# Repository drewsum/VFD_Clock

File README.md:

A VFD clock centered around a PIC32MZ EF microcontroller

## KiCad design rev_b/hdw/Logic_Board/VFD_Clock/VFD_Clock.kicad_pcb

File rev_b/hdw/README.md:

rev B control boards use rev A display boards

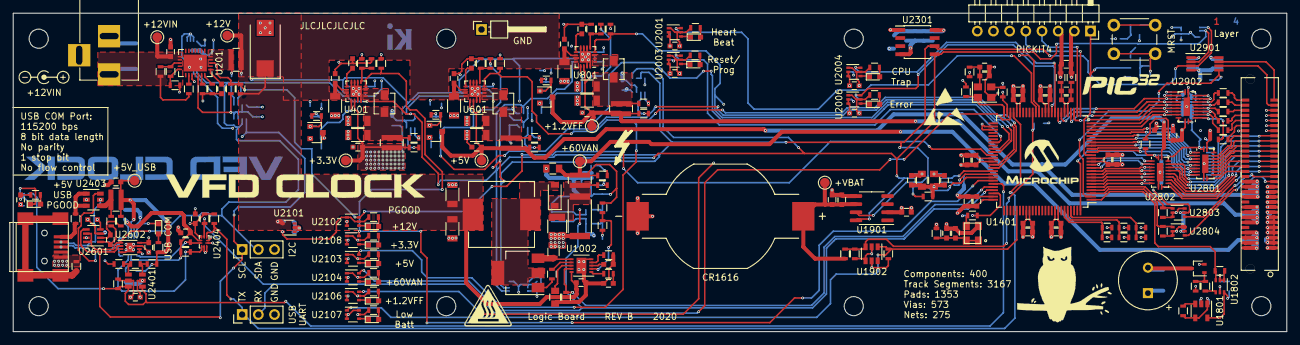
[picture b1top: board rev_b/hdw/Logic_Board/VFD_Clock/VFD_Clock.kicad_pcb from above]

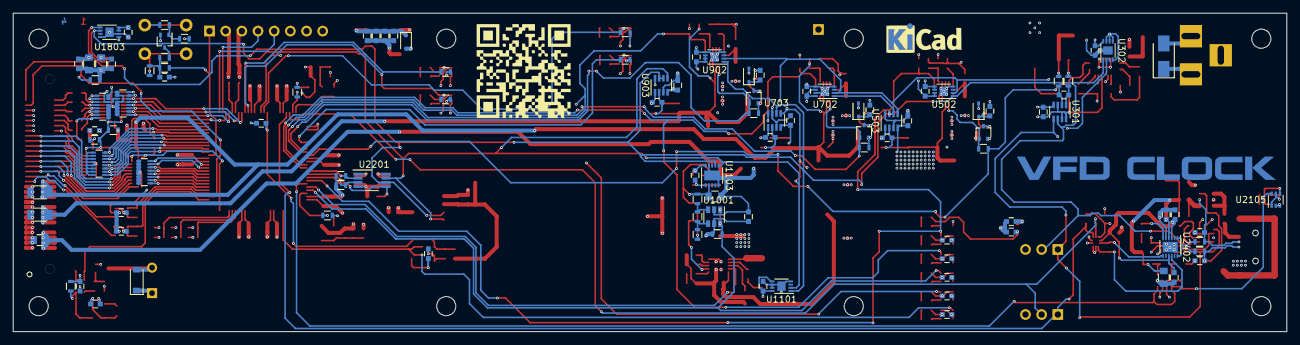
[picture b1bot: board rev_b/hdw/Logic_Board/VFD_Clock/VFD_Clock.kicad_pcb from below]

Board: 4 copper layers, 200.0 x 50.0 mm, 359 parts (109 on the bottom side), 209 nets.

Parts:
BT1902: CR1616_Holder; BAT_BU1632SM-JJ-GTR
BZ1801: CST-931RP-A; MagneticBuzzer_CUI_CST-931RP-A
C201, C402, C602, C802: 10nF; C_0603
C202, C301, C302, C303, C403, C406, C503, C504, C505, C603, C606, C703, C704, C705, C803, C806, C903, C904, C905, C1003, C1004, C1005, C1102, C1104, C1501, C1502, C1601, C1602, C1608, C1609, C1615, C1616, C1622, C1623, C1701, C1702, C1801, C1803, C1804, C1901, C1903, C1904, C1905, C2001, C2003, C2004, C2006, C2101, C2103, C2104, C2105, C2106, C2107, C2108, C2201, C2203, C2304, C2401, C2402, C2403, C2404, C2406, C2407, C2410, C2601, C2602, C2603, C2801, C2802, C2807, C2808, C2901, C2904, C2906: 0.1uF; C_0603
C205: 100uF; CP_Tantalum_Case-X_EIA-7343-43_Reflow
C401, C601, C801, C1001, C1002: 10uF; C_1206
C404, C405, C604, C605, C804, C805, C3002, C3003: 22uF; C_1206
C1007: 6.8nF; C_0603
C1009, C2202, C2204, C2405, C2905, C2907: 4.7uF; C_0805
C1010: 1uF; C_1210
C1011, C1105, C3001: 0.1uF; C_0805
C1301, C1302, C1303, C1603, C1604, C1605, C1606, C1607, C1610, C1617, C1624, C1703, C1704, C1902, C2102, C2301, C2302, C2303: 10uF; C_0603
C2408, C2409: 47pF; C_0603
D201: 24V; D_SMA
D1001, D1801: MBR0580; D_SOD-123
D1301, D1302, D1303, D2301: BAT48JFILM; D_SOD-323
D2001, D2101, D2102, D2103, D2104, D2105, D2107: Green; LED_0603
D2003, D2004, D2006, D2106: Red; LED_0603
D2401: Yellow; LED_0603
H3101, H3102, H3103, H3104, H3105, H3106, H3107, H3108: MountingHole; MountingHole_3mm
J201: +12V IN; BARREL_JACK
J1501: PICKIT4; PICKIT4_Header
J1801: I2C; Pin_Header_Straight_1x03_Pitch2.54mm
J1802: USB UART; Pin_Header_Straight_1x03_Pitch2.54mm
J2401: USB_B_Mini; USB_Mini-B
J3001: DSP_IO_Connector; ERF8-030-07.0-S-DV-K-TR
L401, L601, L801: 2.2uH; L_Vishay_IHLP-1212
L1001: 100uH; L_Vishay_IHLP-4040
L1601, L1602, L1701, L1702, L2401, L2402: 600R 0.5A; L_0603
Q1001: IRFL214TRPBF; SOT-223-3_TabPin2
Q1301, Q1304, Q1307, Q1501, Q1801: BSS214NW; SOT-323_SC-70
Q1302, Q1306, Q1308: ZXMS6004FFTA; SOT-23
R201: 51.1k; R_0603
R202: 1.15k; R_0603
R203, R209: 5.11k; R_0603
R204, R207, R211, R404, R604, R605, R804, R805, R1008, R1009, R1302, R1306, R1310, R1502, R1504, R1701, R1704, R1705, R1802, R1804, R1805, R1807, R1808, R1810, R1903, R2001, R2005, R2006, R2010, R2201, R2202, R2203, R2405, R2903: 10k; R_0603
R205, R210, R405, R407, R606, R608, R806, R808, R1014, R1016, R1501, R1803, R1806, R1809, R1811, R2406, R2410: 10; R_0603
R206, R406, R607, R807, R2407: 0.02; R_0612
R208: 13k; R_0603
R408: 562k; R_0603
R409: 180k; R_0603
R609: 10.5k; R_0603
R610: 2k; R_0603
R809: 75k; R_0603
R810: 150k; R_0603
R1003: 196k; R_0603
R1004: 237; R_0603
R1005: 1.2k; R_0603
R1007: 17.4k; R_0603
R1010: 22k; R_0603
R1011: 2; R_0603
R1012: 0.16; R_0805
R1013: 10k; R_2512
R1015: 1; R_0612
R1017: 36.5k; R_0603
R1018, R1505, R2003, R2007, R2008, R2012, R2101, R2102, R2103, R2104, R2105, R2106, R2107, R2411, R2907, R2908, R2909, R2910, R2911, R2912: 1k; R_0603
R1301, R1503, R1702, R1703: 100; R_0603
R1801, R1901: 1.07M; R_0603
R1902: 220k; R_0603
R2401, R2412, R2413, R2414: 100k; R_0603
R2402: 487k; R_0603
R2403: 6.04k; R_0603
R2404: 40.2k; R_0603
R2408, R2409: 27; R_0603
R2801, R2802, R2803, R2804, R2904: 10K; R_0603
RN2801, RN2802, RN2901, RN2902: 10k; R_Array_Convex_8x0602
SW1501: MRST; SW_PUSH_6mm
TP201: TP; Pin_Header_Angled_1x01_Pitch2.54mm
TP202, TP203: TP_Pad; Test_Point
TP401, TP601, TP801, TP1001, TP1901, TP2401: TP; Test_Point
U201: TPS26600RHFT; QFN-24-1EP_4x5mm_Pitch0.5mm
U301, U503, U703, U903, U2601: INA219BxDCN; SOT-23-8
U302, U502, U702, U902, U1101, U1803, U2602: MCP9804; DFN-8-1EP_3x2mm_P0.5mm_EP1.3x1.5mm
U401, U601, U801: TPS62150A; QFN-16-1EP_3x3mm_P0.5mm_EP1.8x1.8mm
U1001, U1902, U2401: TLV6700; SOT-23-6
U1002: LT3757; DFN-10-1EP_3x3mm_Pitch0.5mm
U1103: LTC4151DD; DFN-10-1EP_3x3mm_Pitch0.5mm
U1401: PIC32MZ2048EFG100_IPT; TQFP-100_14x14mm_Pitch0.5mm
U1801: LTC6900; SOT-23-5
U1802, U2001, U2003, U2004, U2006, U2102, U2103, U2104, U2105, U2106, U2107, U2108, U2803, U2804: 74LVC1G97; SOT-363_SC-70-6
U1901: DS3231MZ; SOIC-8_3.9x4.9mm_P1.27mm
U2101: TPS71533; SOT-353_SC-70-5
U2201, U2901: TCA9803; VSSOP-8_3.0x3.0mm_P0.65mm
U2301: DS1683; SOIC-8_3.9x4.9mm_Pitch1.27mm
U2402: FT234XD; DFN-12-1EP_3x3mm_Pitch0.45mm
U2403: TPD3S014DBVR; SOT-23-6
U2404: SN74AVC2T245; UQFN-10_1.4x1.8mm_Pitch0.4mm
U2801, U2802, U2902: 74VHC541; WQFN-20-1EP_2.5x4.5mm_P0.5mm_EP1x2.9mm
X1701: ASE-8.000MHz; Oscillator_SMD_Abracon_ASE-4Pin_3.2x2.5mm
X1702: ECS-327KE

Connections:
+1.2VFF: C806.1, C3002.1, J3001.12, J3001.14, J3001.16, J3001.18, Q1308.3, R807.2, R808.2, R809.1, TP801.1, U801.14
+3.3VA_MZ: C1607.1, C1623.1, L1601.1, U1401.30
+3.3V_USB: C2402.1, C2407.1, C2410.1, R2413.1, R2414.1, U2402.3, U2402.9, U2404.6
+3V3: BZ1801.1, C302.1, C303.1, C406.1, C503.1, C505.1, C703.1, C705.1, C903.1, C905.1, C1004.1, C1102.1, C1501.1, C1601.1, C1602.1, C1603.1, C1604.1, C1605.1, C1606.1, C1608.1, C1609.1, C1610.1, C1615.1, C1616.1, C1617.1, C1622.1, C1624.1, C1801.1, C1803.1, C1804.1, C1904.1, C1905.1, C2001.1, C2003.1, C2004.1, C2006.1, C2103.1, C2104.1, C2105.1, C2106.1, C2107.1, C2108.1, C2201.1, C2202.1, C2203.1, C2204.1, C2401.1, C2403.1, C2602.1, C2603.1, C2901.1, C2904.1, C2905.1, D1301.2, D1302.2, D1303.2, D1801.1, D2301.2, J1501.2, L1601.2, L1701.2, L1702.2, Q1302.3, R404.1, R406.2, R407.2, R408.1, R604.1, R804.1, R1009.2, R1504.1, R1801.1, R1802.2, R1808.2, R1810.2, R1903.1, R2003.1, R2005.1, R2007.1, R2008.1, R2012.1, R2102.1, R2103.1, R2104.1, R2105.1, R2106.1, R2107.1, R2201.1, R2202.1, R2401.1, R2405.1, R2412.1, R2801.1, R2802.1, R2904.1, RN2901.3, RN2902.6, SW1501.1, TP401.1, U301.4, U302.8, U401.14, U502.7, U502.8, U503.4, U702.6, U702.8, U703.4, U703.8, U902.6, U902.7, U902.8, U903.4, U903.8, U1001.5, U1101.5, U1101.8, U1401.14, U1401.37, U1401.46, U1401.62, U1401.74, U1401.83, U1401.93, U1801.1, U1801.4, U1802.5, U1803.5, U1803.7, U1803.8, U1901.2, U1902.5, U2001.1, U2001.5, U2003.1, U2003.5, U2004.1, U2004.5, U2006.1, U2006.5, U2103.1, U2103.5, U2104.1, U2104.5, U2105.1, U2105.5, U2106.1, U2106.5, U2107.5, U2108.1, U2108.5, U2201.1, U2201.8, U2301.1, U2401.5, U2404.1, U2404.7, U2601.4, U2602.5, U2602.6, U2602.8, U2901.1, U2902.20
+5V: C606.1, C2801.1, C2802.1, C2807.1, C2808.1, C2906.1, C2907.1, C3003.1, J3001.22, J3001.24, J3001.26, J3001.28, Q1306.3, R607.2, R608.2, R609.1, TP601.1, U601.14, U2801.20, U2802.20, U2803.5, U2804.5, U2901.8
+5V_USB: C2404.1, C2405.1, C2406.1, R2402.1, R2406.2, R2407.1, R2411.1, TP2401.1, U2402.4
+12V: C205.1, C401.1, C403.1, C601.1, C603.1, C801.1, C803.1, C1001.1, C1002.1, C1005.1, C2101.1, L1001.1, R206.2, R208.1, R210.2, TP203.1, U401.10, U401.11, U401.12, U601.10, U601.11, U601.12, U801.10, U801.11, U801.12, U1002.10, U2101.4
+12Vin: C202.1, D201.1, J201.1, R201.1, R204.1, TP202.1, U201.8, U201.9
+60VAN: C1011.1, C1105.1, C3001.1, J3001.2, J3001.4, J3001.6, J3001.8, R1003.1, R1015.2, R1016.1, R1017.1, TP1001.1, U1103.2
/USB UART Bridge/BRIDGE_USB+: R2408.2, U2402.12
/USB UART Bridge/BRIDGE_USB-: R2409.2, U2402.1
/USB UART Bridge/CONN_USB+: C2408.1, J2401.3, R2408.1, U2403.6
/USB UART Bridge/CONN_USB-: C2409.1, J2401.2, R2409.1, U2403.5
Anode_A: RN2801.16, U1401.23, U2801.2
Anode_A_DSP: J3001.46, U2801.18
Anode_B: RN2801.15, U1401.22, U2801.3
Anode_B_DSP: J3001.44, U2801.17
Anode_C: RN2801.14, U1401.21, U2801.4
Anode_C_DSP: J3001.42, U2801.16
Anode_D: RN2801.13, U1401.20, U2801.5
Anode_DP: RN2801.9, U1401.16, U2801.9
Anode_DP_DSP: J3001.32, U2801.11
Anode_D_DSP: J3001.40, U2801.15
Anode_E: RN2801.12, U1401.19, U2801.6
Anode_E_DSP: J3001.38, U2801.14
Anode_F: RN2801.11, U1401.18, U2801.7
Anode_F_DSP: J3001.36, U2801.13
Anode_G: RN2801.10, U1401.17, U2801.8
Anode_G_DSP: J3001.34, U2801.12
Backup_RTC_Config: R1810.1, R1811.1, U1401.96
Buzzer_Enable: R1805.2, U1401.1, U1802.3
CPU_Exception_LED: R2006.1, U1401.34, U2004.6
Cap_Touch_Down: RN2901.12, U1401.29, U2902.15
Cap_Touch_Down_DSP: J3001.56, R2910.1
Cap_Touch_Left: RN2901.9, U1401.24, U2902.18
Cap_Touch_Left_DSP: J3001.50, R2907.1
Cap_Touch_Power: RN2901.13, U1401.32, U2902.14
Cap_Touch_Power_DSP: J3001.58, R2911.1
Cap_Touch_Right: RN2901.10, U1401.25, U2902.17
Cap_Touch_Right_DSP: J3001.52, R2908.1
Cap_Touch_Up: RN2901.11, U1401.28, U2902.16
Cap_Touch_Up_DSP: J3001.54, R2909.1
Colon_0: RN2802.10, U1401.6, U2802.8
Colon_0_DSP: J3001.33, U2802.12
Colon_1: RN2802.9, U1401.5, U2802.9
Colon_1_DSP: J3001.31, U2802.11
Colon_2: R2803.1, U1401.4, U2803.1
Colon_2_DSP: J3001.29, U2803.4
Colon_3: R2804.1, U1401.3, U2804.1
Colon_3_DSP: J3001.27, U2804.4
Error_LED: R2010.1, U1401.35, U2006.6
GND: BT1902.2, C202.2, C205.2, C302.2, C303.2, C401.2, C402.2, C403.2, C404.2, C405.2, C406.2, C503.2, C505.2, C601.2, C602.2, C603.2, C604.2, C605.2, C606.2, C703.2, C705.2, C801.2, C802.2, C803.2, C804.2, C805.2, C806.2, C903.2, C905.2, C1001.2, C1002.2, C1003.2, C1004.2, C1005.2, C1007.2, C1009.2, C1010.2, C1011.2, C1102.2, C1105.2, C1301.2, C1302.2, C1303.2, C1501.2, C1502.2, C1601.2, C1602.2, C1603.2, C1604.2, C1605.2, C1606.2, C1608.2, C1609.2, C1610.2, C1615.2, C1616.2, C1617.2, C1622.2, C1624.2, C1701.2, C1702.2, C1703.2, C1704.2, C1801.2, C1803.2, C1804.2, C1901.2, C1902.2, C1903.2, C1904.2, C1905.2, C2001.2, C2003.2, C2004.2, C2006.2, C2101.2, C2102.2, C2103.2, C2104.2, C2105.2, C2106.2, C2107.2, C2108.2, C2201.2, C2202.2, C2203.2, C2204.2, C2301.2, C2302.2, C2303.2, C2304.2, C2401.2, C2402.2, C2403.2, C2404.2, C2405.2, C2406.2, C2407.2, C2408.2, C2409.2, C2410.2, C2602.2, C2603.2, C2801.2, C2802.2, C2807.2, C2808.2, C2901.2, C2904.2, C2905.2, C2906.2, C2907.2, C3001.2, C3002.2, C3003.2, D201.2, J201.2, J201.3, J1501.3, J1801.3, J1802.3, J2401.5, J3001.1, J3001.3, J3001.5, J3001.7, J3001.9, J3001.11, J3001.13, J3001.15, J3001.17, J3001.19, J3001.21, J3001.23, J3001.25, J3001.47, J3001.48, J3001.49, J3001.51, J3001.53, J3001.55, L1602.2, L2402.1, Q1301.2, Q1302.2, Q1304.2, Q1306.2, Q1307.2, Q1308.2, Q1501.2, Q1801.2, R209.2, R409.2, R605.2, R610.2, R805.2, R810.2, R1005.2, R1007.2, R1008.2, R1012.2, R1013.2, R1018.2, R1502.2, R1701.2, R1704.2, R1705.2, R1803.2, R1804.1, R1805.1, R1807.1, R1809.2, R1811.2, R1902.2, R2001.2, R2006.2, R2010.2, R2203.2, R2404.2, R2803.2, R2804.2, R2903.2, RN2801.1, RN2801.2, RN2801.3, RN2801.4, RN2801.5, RN2801.6, RN2801.7, RN2801.8, RN2802.1, RN2802.2, RN2802.3, RN2802.4, RN2802.5, RN2802.6, RN2802.7, RN2802.8, RN2901.1, RN2901.2, RN2901.4, RN2901.5, RN2901.6, RN2901.7, RN2901.8, RN2902.1, RN2902.2, RN2902.3, RN2902.4, RN2902.5, RN2902.7, RN2902.8, TP201.1, U201.17, U301.3, U301.7, U301.8, U302.4, U302.5, U302.6, U302.7, U302.9, U401.6, U401.7, U401.8, U401.15, U401.16, U401.17, U502.4, U502.5, U502.6, U502.9, U503.3, U503.8, U601.6, U601.7, U601.8, U601.15, U601.16, U601.17, U702.4, U702.5, U702.7, U702.9, U703.3, U703.7, U801.6, U801.7, U801.8, U801.15, U801.16, U801.17, U902.4, U902.5, U902.9, U903.3, U1001.2, U1002.5, U1002.11, U1101.4, U1101.6, U1101.7, U1101.9, U1103.5, U1103.9, U1103.11, U1401.13, U1401.36, U1401.45, U1401.52, U1401.53, U1401.63, U1401.75, U1401.84, U1401.92, U1801.2, U1802.1, U1802.2, U1803.4, U1803.6, U1803.9, U1901.5, U1902.2, U1902.4, U2001.2, U2001.3, U2003.2, U2003.3, U2004.2, U2004.3, U2006.2, U2006.3, U2101.2, U2102.2, U2102.3, U2103.2, U2103.3, U2104.2, U2104.3, U2105.2, U2105.3, U2106.2, U2106.3, U2107.2, U2107.3, U2107.6, U2108.2, U2108.3, U2201.4, U2301.4, U2401.2, U2402.5, U2402.13, U2403.2, U2404.2, U2404.3, U2404.10, U2601.3, U2601.7, U2602.4, U2602.7, U2602.9, U2801.10, U2801.21, U2802.10, U2802.21, U2803.2, U2803.3, U2803.6, U2804.2, U2804.3, U2804.6, U2901.4, U2902.10, U2902.21, X1701.2, X1702.2
GNDA_MZ: C1607.2, C1623.2, L1602.1, U1401.31
Grid_0: RN2802.16, U1401.12, U2802.2
Grid_0_DSP: J3001.45, U2802.18
Grid_1: RN2802.15, U1401.11, U2802.3
Grid_1_DSP: J3001.43, U2802.17
Grid_2: RN2802.14, U1401.10, U2802.4
Grid_2_DSP: J3001.41, U2802.16
Grid_3: RN2802.13, U1401.9, U2802.5
Grid_3_DSP: J3001.39, U2802.15
Grid_4: RN2802.12, U1401.8, U2802.6
Grid_4_DSP: J3001.37, U2802.14
Grid_5: RN2802.11, U1401.7, U2802.7
Grid_5_DSP: J3001.35, U2802.13
Heartbeat_LED: R2001.1, U1401.40, U2001.6
I2C_DSP_EN: R2903.1, U1401.2, U2901.5
I2C_DSP_SCL: J3001.59, U2901.7
I2C_DSP_SDA: J3001.57, U2901.6
I2C_EN: R2203.1, U1401.68, U2201.5
I2C_MCU_SCL: R2201.2, U1401.66, U2201.2
I2C_MCU_SDA: R2202.2, U1401.67, U2201.3
I2C_SCL: J1801.1, U301.5, U302.2, U502.2, U503.5, U702.2, U703.5, U902.2, U903.5, U1101.2, U1103.6, U1803.2, U1901.8, U2201.7, U2301.5, U2601.5, U2602.2, U2901.2
I2C_SDA: J1801.2, U301.6, U302.1, U502.1, U503.6, U503.7, U702.1, U703.6, U902.1, U903.6, U903.7, U1101.1, U1103.7, U1803.1, U1901.7, U2201.6, U2301.6, U2601.6, U2601.8, U2602.1, U2901.3
ICSPCLK: J1501.5, U1401.26
ICSPDAT: J1501.4, U1401.27
MCU_POSC: R1702.2, R1704.1, U1401.49
MCU_POSC_Enable: R1701.1, U1401.50, X1701.1
MCU_SOSC: R1703.2, R1705.1, U1401.73
unnamed: BZ1801.2, D1801.2, Q1801.3
unnamed: C201.1, U201.20
unnamed: C201.2, R203.2, R207.2, R211.2, U201.15, U201.25
unnamed: C402.1, U401.9
unnamed: C404.1, C405.1, L401.2, R405.2, R406.1
unnamed: C602.1, U601.9
unnamed: C604.1, C605.1, L601.2, R606.2, R607.1
unnamed: C802.1, U801.9
unnamed: C804.1, C805.1, L801.2, R806.2, R807.1
unnamed: C1003.1, U1002.3
unnamed: C1007.1, R1010.2
unnamed: C1009.1, U1002.8
unnamed: C1010.1, D1001.1, R1013.1, R1014.1, R1015.1
unnamed: C1301.1, D1301.1, R1302.2
unnamed: C1302.1, D1302.1, R1306.2
unnamed: C1303.1, D1303.1, R1310.2
unnamed: C1502.1, R1503.1, R1504.2, R1505.2
unnamed: C1701.1, C1703.1, L1701.1, X1701.4
unnamed: C1702.1, C1704.1, L1702.1, X1702.1, X1702.4
unnamed: C2102.1, R2101.1, U2101.5, U2102.1, U2102.5
unnamed: C2301.1, C2302.1, C2303.1, C2304.1, D2301.1, U2301.8
unnamed: D1001.2, L1001.2, Q1001.2
unnamed: D2001.1, U2001.4
unnamed: D2001.2, R2003.2
unnamed: D2003.1, U2003.4
unnamed: D2003.2, R2007.2
unnamed: D2004.1, U2004.4
unnamed: D2004.2, R2008.2
unnamed: D2006.1, U2006.4
unnamed: D2006.2, R2012.2
unnamed: D2101.1, U2102.4
unnamed: D2101.2, R2101.2
unnamed: D2102.1, U2103.4
unnamed: D2102.2, R2102.2
unnamed: D2103.1, U2104.4
unnamed: D2103.2, R2103.2
unnamed: D2104.1, U2105.4
unnamed: D2104.2, R2104.2
unnamed: D2105.1, U2106.4
unnamed: D2105.2, R2105.2
unnamed: D2106.1, U2107.4
unnamed: D2106.2, R2106.2
unnamed: D2107.1, U2108.4
unnamed: D2107.2, R2107.2
unnamed: D2401.2, R2411.2
unnamed: J2401.1, L2401.1
unnamed: J2401.6, L2402.2
unnamed: L401.1, U401.1, U401.2, U401.3
unnamed: L601.1, U601.1, U601.2, U601.3
unnamed: L801.1, U801.1, U801.2, U801.3
unnamed: L2401.2, U2403.1, U2403.3
unnamed: Q1001.1, R1011.1
unnamed: Q1001.3, R1012.1, U1002.6
unnamed: Q1301.3, Q1302.1, R1302.1
unnamed: Q1304.3, Q1306.1, R1306.1
unnamed: Q1307.3, Q1308.1, R1310.1
unnamed: Q1501.1, R1501.2, R1502.1
unnamed: Q1501.3, R1503.2
unnamed: Q1801.1, R1806.1, R1807.2
unnamed: R201.2, R202.1, U201.10
unnamed: R202.2, R203.1, U201.12
unnamed: R204.2, U201.14
unnamed: R205.2, R206.1, U201.23, U201.24
unnamed: R207.1, U201.19
unnamed: R211.1, U201.18
unnamed: R408.2, R409.1, U401.5
unnamed: R609.2, R610.1, U601.5
unnamed: R809.2, R810.1, U801.5
unnamed: R1003.2, R1004.1, U1001.3
unnamed: R1004.2, R1005.1, U1001.4
unnamed: R1007.1, U1002.4
unnamed: R1010.1, U1002.1
unnamed: R1011.2, U1002.7
unnamed: R1017.2, R1018.1, U1002.2
unnamed: R1501.1, SW1501.2
unnamed: R1702.1, X1701.3
unnamed: R1703.1, X1702.3
unnamed: R1801.2, U1801.3
unnamed: R1804.2, U1801.5, U1802.6
unnamed: R1806.2, U1802.4
unnamed: R2402.2, R2403.1, U2401.3
unnamed: R2403.2, R2404.1, U2401.4
unnamed: R2407.2, R2410.2, U2403.4
unnamed: R2907.2, RN2902.16, U2902.2
unnamed: R2908.2, RN2902.15, U2902.3
unnamed: R2909.2, RN2902.14, U2902.4
unnamed: R2910.2, RN2902.13, U2902.5
unnamed: R2911.2, RN2902.12, U2902.6
unnamed: R2912.2, RN2902.11, U2902.7
unnamed: RN2901.15, U2902.12
unnamed: RN2901.16, U2902.11
unnamed: RN2902.9, U2902.9
unnamed: RN2902.10, U2902.8
POS1P2_VFF_PGOOD: R804.2, U801.4, U1401.60, U2106.6
POS1P2_VFF_RUN: Q1307.1, R805.1, U801.13, U1401.59
POS1P2_VFF_SNS_OUT+: C904.1, R806.1, U903.1
POS1P2_VFF_SNS_OUT-: C904.2, R808.1, U903.2
POS3P3_PGOOD: R404.2, U401.4, U1401.69, U2108.6
POS3P3_RUN: Q1301.1, R1301.1, U401.13
POS3P3_SNS_OUT+: C504.1, R405.1, U503.1
POS3P3_SNS_OUT-: C504.2, R407.1, U503.2
POS5_PGOOD: R604.2, U601.4, U1401.65, U2103.6
POS5_RUN: Q1304.1, R605.1, U601.13, U1401.64
POS5_SNS_OUT+: C704.1, R606.1, U703.1
POS5_SNS_OUT-: C704.2, R608.1, U703.2
POS5_USB_PGOOD: R2405.2, U1401.70, U2105.6, U2401.1, U2401.6
POS5_USB_SNS+: C2601.1, R2410.1, U2601.1
POS5_USB_SNS-: C2601.2, R2406.1, U2601.2
POS12_PGOOD: R208.2, R209.1, R1301.2, U201.22, U1401.61, U2102.6
POS12_SNS+: C301.1, R205.1, U301.1
POS12_SNS-: C301.2, R210.1, U301.2
POS60_VAN_PGOOD: R1009.1, U1001.1, U1001.6, U1401.72, U2104.6
POS60_VAN_RUN: R1008.1, U1002.9, U1401.71
POS60_VAN_SNS_OUT+: C1104.1, R1014.2, U1103.1
POS60_VAN_SNS_OUT-: C1104.2, R1016.2, U1103.10
Reset_LED: R2005.2, U1401.57, U2003.6
TOF_Config: R1808.1, R1809.1, U1401.97
Telemetry_Config: R1802.1, R1803.1, U1401.95
USB_UART_RX: J1802.2, R2412.2, U1401.48, U2404.8
USB_UART_RX_BUF: R2413.2, U2402.7, U2404.5
USB_UART_TX: J1802.1, R2401.2, U1401.47, U2404.9
USB_UART_TX_BUF: R2414.2, U2402.10, U2404.4
VBAT: BT1902.1, C1902.1, C1903.1, R1901.1, TP1901.1, U1901.6
VBAT_ADC: C1901.1, R1901.2, R1902.1, U1401.41, U1902.3
VBAT_PGOOD: R1903.2, U1401.80, U1902.1, U2107.1
~Display_Detect: RN2901.14, U1401.33, U2902.13
~Display_Detect_DSP: J3001.60, R2912.1
~IO_Level_Shift_Enable: R2801.2, R2802.2, R2904.2, U1401.100, U2801.1, U2801.19, U2802.1, U2802.19, U2902.1, U2902.19
~MCLR: J1501.1, R1505.1, U1401.15
~USB_ACTIVE: D2401.1, U2402.6

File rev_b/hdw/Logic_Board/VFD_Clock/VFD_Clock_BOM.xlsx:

Qty | Reference(s) | Value | Config | Digi-Key PN
1 | BT1901 | CR1616 | Backup_RTC | P034-ND
1 | BT1902 | CR1616_Holder | Backup_RTC | BU1632SM-JJ-GCT-ND
1 | BZ1801 | CST-931RP-A |  | 102-1461-ND
4 | C201, C402, C602, C802 | 10nF |  | 399-7842-1-ND
74 | C202, C301, C302, C303, C403, C406, C503, C504, C505, C603, C606, C703, C704, C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 | 0.1uF |  | 399-7845-1-ND
1 | C205 | 100uF |  | 718-1102-1-ND
5 | C401, C601, C801, C1001, C1002 | 10uF |  | 1276-7031-1-ND
8 | C404, C405, C604, C605, C804, C805, C3002, C3003 | 22uF |  | 1276-3148-1-ND
1 | C1007 | 6.8nF |  | 311-1084-1-ND
6 | C1009, C2202, C2204, C2405, C2905, C2907 | 4.7uF |  | 1276-2970-1-ND
1 | C1010 | 1uF |  | 490-1857-1-ND
3 | C1011, C1105, C3001 | 0.1uF |  | 490-4789-1-ND
18 | C1301, C1302, C1303, C1603, C1604, C1605, C1606, C1607, C1610, C1617, C1624, C1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 | 10uF |  | 490-12538-1-ND
2 | C2408, C2409 | 47pF |  | 478-1171-1-ND
1 | D201 | 24V |  | SMAJ24CALFCT-ND
2 | D1001, D1801 | MBR0580 |  | MBR0580S1-7DICT-ND
4 | D1301, D1302, D1303, D2301 | BAT48JFILM
7 | D2001, D2101, D2102, D2103, D2104, D2105, D2107 | Green |  | 160-1446-1-ND
4 | D2003, D2004, D2006, D2106 | Red |  | 160-1447-1-ND
1 | J201 | +12V IN
1 | J1501 | PICKIT4
1 | J1801 | I2C
1 | J1802 | USB UART
1 | J2401 | USB_B_Mini |  | 732-2109-1-ND
1 | J3001 | DSP_IO_Connector |  | ERF8-030-07.0-S-DV-K-TR
3 | L401, L601, L801 | 2.2uH |  | 541-1322-1-ND
1 | L1001 | 100uH |  | 541-1310-1-ND
6 | L1601, L1602, L1701, L1702, L2401, L2402 | 600R 0.5A |  | 732-2389-1-ND
24 | MK3101, MK3102, MK3103, MK3104, MK3105, MK3106, MK3109, MK3110, MK3111, MK3112,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 | Standoff |  | 1772-2080-ND
8 | MK3107, MK3108, MK3115, MK3116, MK3123, MK3124, MK3131, MK3132 | Screw |  | 36-9900-ND
1 | N201 | +12V 1A Power Supply |  | 993-1335-ND
1 | Q1001 | IRFL214TRPBF |  | IRFL214PBFCT-ND
5 | Q1301, Q1304, Q1307, Q1501, Q1801 | BSS214NW |  | BSS214NWH6327XTSA1CT-ND
3 | Q1302, Q1306, Q1308 | ZXMS6004FFTA |  | ZXMS6004FFCT-ND
1 | R201 | 51.1k |  | RMCF0603FT51K1TR-ND
1 | R202 | 1.15k |  | RMCF0603FT1K15CT-ND
2 | R203, R209 | 5.11k |  | CR0603-FX-5111ELFCT-ND
34 | R204, R207, R211, R404, R604, R605, R804, R805, R1008, R1009, R1302, R1306, R13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 | 10k |  | YAG2321CT-ND
17 | R205, R210, R405, R407, R606, R608, R806, R808, R1014, R1016, R1501, R1803, R18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 | 10 | Telemetry | YAG2321CT-ND
5 | R206, R406, R607, R807, R2407 | 0.02 |  | P16010CT-ND
1 | R208 | 13k |  | 311-13.0KHRCT-ND
1 | R408 | 562k |  | 311-562KHRCT-ND
1 | R409 | 180k |  | 749-1763-1-ND
1 | R609 | 10.5k |  | 311-10.5KHRCT-ND
1 | R610 | 2k |  | 311-2.00KHRCT-ND
1 | R809 | 75k |  | 749-1681-1-ND
1 | R810 | 150k |  | A129714CT-ND
1 | R1003 | 196k |  | P196KHCT-ND
1 | R1004 | 237 |  | 541-237HCT-ND
1 | R1005 | 1.2k |  | P1.20KHCT-ND
1 | R1007 | 17.4k |  | 311-17.4KHRCT-ND
1 | R1010 | 22k |  | A129704CT-ND
1 | R1011 | 2 |  | 541-2.00SCT-ND
1 | R1012 | 0.16 |  | P.16BJCT-ND
1 | R1013 | 10k |  | 541-10.0KAFCT-ND
1 | R1015 | 1 |  | RHM1220CT-ND
1 | R1017 | 36.5k |  | RMCF0603FT36K5CT-ND
20 | R1018, R1505, R2003, R2007, R2008, R2012, R2101, R2102, R2103, R2104, R2105, R2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 | 1k |  | RMCF0603FT1K00CT-ND
4 | R1301, R1503, R1702, R1703 | 100 |  | A106047CT-ND
2 | R1801, R1901 | 1.07M |  | 541-1.07MHCT-ND
1 | R1902 | 220k |  | RMCF0603FT220KCT-ND
4 | R2401, R2412, R2413, R2414 | 100k |  | A106046CT-ND
1 | R2402 | 487k |  | 311-487KHRCT-ND
1 | R2403 | 6.04k |  | RMCF0603FT6K04CT-ND
1 | R2404 | 40.2k |  | 311-40.2KHRCT-ND
2 | R2408, R2409 | 27 |  | RMCF0603FT27R0CT-ND
5 | R2801, R2802, R2803, R2804, R2904 | 10K |  | RHM10KADCT-ND
4 | RN2801, RN2802, RN2901, RN2902 | 10k |  | Y1103CT-ND
1 | SW1501 | MRST
1 | U201 | TPS26600RHFT |  | 296-45478-1-ND
5 | U301, U503, U703, U903, U2601 | INA219BxDCN | Telemetry | 296-46420-1-ND
7 | U302, U502, U702, U902, U1101, U1803, U2602 | MCP9804 | Telemetry | MCP9804T-E/MCCT-ND
3 | U401, U601, U801 | TPS62150A |  | 296-41757-1-ND
2 | U1001, U2401 | TLV6700 |  | 296-51696-1-ND
1 | U1002 | LT3757 |  | LT3757EDD#PBF-ND
1 | U1103 | LTC4151DD |  | LTC4151CDD#PBF-ND
1 | U1401 | PIC32MZ2048EFG100_IPT | ALL | PIC32MZ2048EFG100-I/PT-ND
1 | U1801 | LTC6900 |  | LTC6900CS5#TRMPBFCT-ND
1 | U1802 | 74LVC1G97 |  | 296-15582-1-ND
1 | U1901 | DS3231MZ | Backup_RTC | DS3231MZ+-ND
1 | U1902 | TLV6700 |  | 296-51696-1-ND
10 | U2001, U2003, U2004, U2006, U2102, U2103, U2104, U2105, U2106, U2108 | 74LVC1G97 |  | 296-15582-1-ND
1 | U2101 | TPS71533 |  | 296-12008-1-ND
3 | U2107, U2803, U2804 | 74LVC1G97 |  | 296-15582-1-ND
2 | U2201, U2901 | TCA9803 |  | 296-47829-1-ND
1 | U2301 | DS1683 | TOF | DS1683S+-ND
1 | U2402 | FT234XD |  | 768-1178-1-ND
1 | U2403 | TPD3S014DBVR |  | 296-38835-1-ND
1 | U2404 | SN74AVC2T245 |  | 296-23684-1-ND
3 | U2801, U2802, U2902 | 74VHC541 |  | 1727-7068-1-ND
1 | X1701 | ASE-8.000MHz |  | 535-9558-1-ND
1 | X1702 | ECS-327KE |  | XC1751CT-ND

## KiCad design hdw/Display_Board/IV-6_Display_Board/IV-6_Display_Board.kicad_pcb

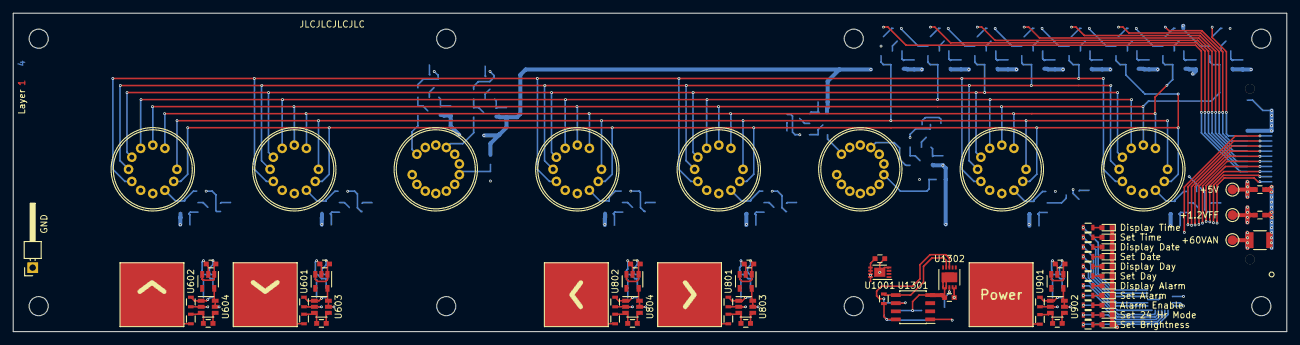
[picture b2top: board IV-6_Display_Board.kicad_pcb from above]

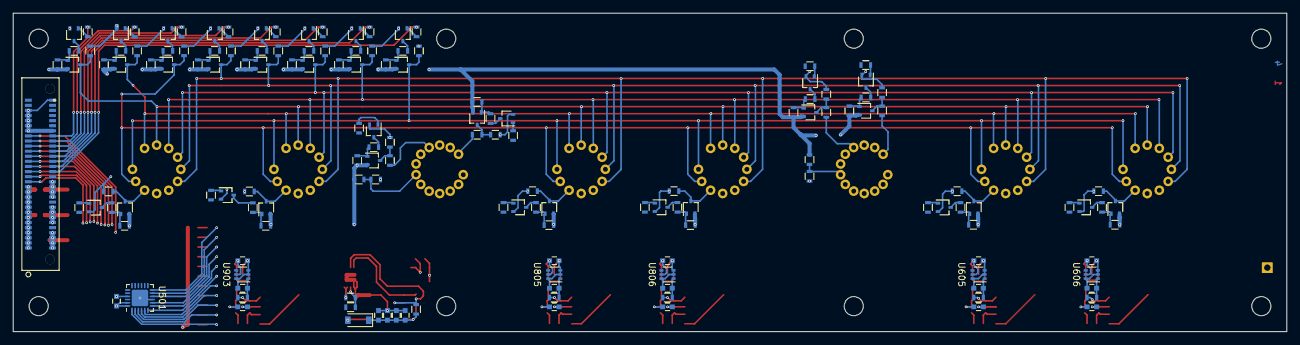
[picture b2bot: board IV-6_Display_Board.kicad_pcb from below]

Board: 4 copper layers, 200.0 x 50.0 mm, 238 parts (152 on the bottom side), 163 nets.

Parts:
C501, C601, C602, C605, C606, C609, C610, C801, C802, C805, C806, C809, C810, C901, C903, C905, C1001, C1304, C1305: 0.1uF; C_0603
C603, C604, C803, C804, C902: 10nF; C_0603
C607, C608, C807, C808, C904, C1201, C1202, C1301, C1302, C1303: 10uF; C_0603
C1203: 1uF; C_1210
D501, D502, D503, D504, D505, D506, D507, D508, D509, D510, D511: Cyan; LED_0603
D1301: MBR0530; D_SOD-123
H1401, H1402, H1403, H1404, H1405, H1406, H1407, H1408: MountingHole; MountingHole_3mm
J3001: DSP_IO_Connector; ERM8-030-09.0-L-DV-TR
Q201, Q202, Q205, Q206, Q209, Q210, Q213, Q214, Q301, Q302, Q305, Q306, Q309, Q310, Q1101, Q1103, Q1105, Q1107: PMSTA06; SOT-323_SC-70
Q203, Q204, Q207, Q208, Q211, Q212, Q215, Q216, Q303, Q304, Q307, Q308, Q311, Q312, Q1102, Q1104, Q1106, Q1108: BC856W; SOT-323_SC-70
R201, R202, R209, R210, R217, R218, R225, R226, R301, R302, R309, R310, R317, R318, R603, R604, R605, R606, R803, R804, R805, R806, R902, R903, R1101, R1105, R1106, R1107, R1108, R1112, R1113, R1114, R1115, R1119, R1120, R1124, R1301, R1302: 10k; R_0603
R203, R205, R211, R213, R219, R221, R227, R229, R303, R305, R311, R313, R319, R321, R1102, R1109, R1116, R1121: 220k; R_0603
R204, R206, R212, R214, R220, R222, R228, R230, R304, R306, R312, R314, R320, R322, R1103, R1110, R1117, R1122: 68k; R_0603
R207, R208, R215, R216, R223, R224, R231, R232, R307, R308, R315, R316, R323, R324, R1104, R1111, R1118, R1123: 100k; R_0603
R501, R502, R503, R504, R505, R506, R507, R508, R509, R510, R511, R601, R602, R801, R802, R901: 499; R_0603
R1303: 392k; R_0603
R1304: 1M; R_0603
SW601, SW602, SW801, SW802, SW901: Cap_Touch; Capacitive_Touch_Pad
TP701, TP702, TP703: TP_Pad; Test_Point
TP704: TP; PinHeader_1x01_P2.54mm_Horizontal
U501: TCA9555RGER; QFN-24-1EP_4x4mm_P0.5mm_EP2.6x2.6mm
U601, U602, U801, U802, U901: TLV71333PDBV; SOT-23-5
U603, U604, U803, U804, U902: AT42QT1010-TSHR; SOT-23-6
U605, U606, U805, U806, U903: 74LVC1G97; SOT-363_SC-70-6
U1001: MCP9804; DFN-8-1EP_3x2mm_P0.5mm_EP1.75x1.45mm
U1301: DS1683; SOIC-8_3.9x4.9mm_Pitch1.27mm
U1302: LTC4316DD; DFN-10-1EP_3x3mm_Pitch0.5mm
VFD401, VFD402, VFD403, VFD404, VFD405, VFD406: IV-6
VFD1101, VFD1102: IV-1

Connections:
24HR_Mode_LED: R510.1, U501.2
+1.2VFF: C1202.1, J3001.12, J3001.14, J3001.16, J3001.18, TP702.1, VFD401.8, VFD402.8, VFD403.8, VFD404.8, VFD405.8, VFD406.8, VFD1101.8, VFD1102.8
+5V: C501.1, C601.1, C602.1, C609.1, C610.1, C801.1, C802.1, C809.1, C810.1, C901.1, C905.1, C1001.1, C1201.1, C1305.1, D1301.2, J3001.22, J3001.24, J3001.26, J3001.28, R1304.1, TP703.1, U501.21, U601.1, U601.3, U602.1, U602.3, U605.5, U606.5, U801.1, U801.3, U802.1, U802.3, U805.5, U806.5, U901.1, U901.3, U903.5, U1001.5, U1001.6, U1001.7, U1001.8, U1301.1, U1302.4, U1302.5
+60VAN: C1203.1, J3001.2, J3001.4, J3001.6, J3001.8, Q203.2, Q204.2, Q207.2, Q208.2, Q211.2, Q212.2, Q215.2, Q216.2, Q303.2, Q304.2, Q307.2, Q308.2, Q311.2, Q312.2, Q1102.2, Q1104.2, Q1106.2, Q1108.2, R203.1, R205.1, R211.1, R213.1, R219.1, R221.1, R227.1, R229.1, R303.1, R305.1, R311.1, R313.1, R319.1, R321.1, R1102.1, R1106.1, R1109.1, R1113.1, R1116.1, R1121.1, TP701.1
Alarm_Enable_LED: R509.1, U501.3
Anode_A_DSP: J3001.46, R226.1
Anode_A_VFD: Q216.3, R232.1, VFD401.2, VFD402.2, VFD403.2, VFD404.2, VFD405.2, VFD406.2
Anode_B_DSP: J3001.44, R218.1
Anode_B_VFD: Q212.3, R224.1, VFD401.1, VFD402.1, VFD403.1, VFD404.1, VFD405.1, VFD406.1
Anode_C_DSP: J3001.42, R210.1
Anode_C_VFD: Q208.3, R216.1, VFD401.10, VFD402.10, VFD403.10, VFD404.10, VFD405.10, VFD406.10
Anode_DP_DSP: J3001.32, R217.1
Anode_DP_VFD: Q211.3, R223.1, VFD401.11, VFD402.11, VFD403.11, VFD404.11, VFD405.11, VFD406.11
Anode_D_DSP: J3001.40, R202.1
Anode_D_VFD: Q204.3, R208.1, VFD401.6, VFD402.6, VFD403.6, VFD404.6, VFD405.6, VFD406.6
Anode_E_DSP: J3001.38, R209.1
Anode_E_VFD: Q207.3, R215.1, VFD401.5, VFD402.5, VFD403.5, VFD404.5, VFD405.5, VFD406.5
Anode_F_DSP: J3001.36, R225.1
Anode_F_VFD: Q215.3, R231.1, VFD401.4, VFD402.4, VFD403.4, VFD404.4, VFD405.4, VFD406.4
Anode_G_DSP: J3001.34, R201.1
Anode_G_VFD: Q203.3, R207.1, VFD401.3, VFD402.3, VFD403.3, VFD404.3, VFD405.3, VFD406.3
Cap_Touch_Down_DSP: J3001.56, U605.4
Cap_Touch_Left_DSP: J3001.50, U806.4
Cap_Touch_Power_DSP: J3001.58, U903.4
Cap_Touch_Right_DSP: J3001.52, U805.4
Cap_Touch_Up_DSP: J3001.54, U606.4
Colon_0_DSP: J3001.33, R1101.1
Colon_0_VFD: R1105.1, VFD1101.13
Colon_1_DSP: J3001.31, R1108.1
Colon_1_VFD: R1112.1, VFD1101.10
Colon_2_DSP: J3001.29, R1115.1
Colon_2_VFD: R1119.1, VFD1102.13
Colon_3_DSP: J3001.27, R1120.1
Colon_3_VFD: R1124.1, VFD1102.10
Display_Alarm_LED: R507.1, U501.5
Display_Date_LED: R503.1, U501.10
Display_Time_LED: R501.1, U501.12
Display_Weekday_LED: R505.1, U501.7
GND: C501.2, C601.2, C602.2, C605.2, C606.2, C607.2, C608.2, C609.2, C610.2, C801.2, C802.2, C805.2, C806.2, C807.2, C808.2, C809.2, C810.2, C901.2, C903.2, C904.2, C905.2, C1001.2, C1201.2, C1202.2, C1203.2, C1301.2, C1302.2, C1303.2, C1304.2, C1305.2, D501.1, D502.1, D503.1, D504.1, D505.1, D506.1, D507.1, D508.1, D509.1, D510.1, D511.1, J3001.1, J3001.3, J3001.5, J3001.7, J3001.9, J3001.11, J3001.13, J3001.15, J3001.17, J3001.19, J3001.21, J3001.23, J3001.25, J3001.47, J3001.48, J3001.49, J3001.51, J3001.53, J3001.55, J3001.60, Q201.2, Q202.2, Q205.2, Q206.2, Q209.2, Q210.2, Q213.2, Q214.2, Q301.2, Q302.2, Q305.2, Q306.2, Q309.2, Q310.2, Q1101.2, Q1103.2, Q1105.2, Q1107.2, R207.2, R208.2, R215.2, R216.2, R223.2, R224.2, R231.2, R232.2, R307.2, R308.2, R315.2, R316.2, R323.2, R324.2, R603.2, R604.2, R803.2, R804.2, R902.2, R1104.2, R1107.2, R1111.2, R1114.2, R1118.2, R1123.2, R1303.2, TP704.1, U501.9, U501.18, U501.23, U501.24, U501.25, U601.2, U602.2, U603.2, U604.2, U605.2, U605.3, U605.6, U606.2, U606.3, U606.6, U801.2, U802.2, U803.2, U804.2, U805.2, U805.3, U805.6, U806.2, U806.3, U806.6, U901.2, U902.2, U903.2, U903.3, U903.6, U1001.4, U1001.9, U1301.4, U1302.1, U1302.2, U1302.11, VFD401.7, VFD402.7, VFD403.7, VFD404.7, VFD405.7, VFD406.7, VFD1101.1, VFD1102.1
Grid_0_DSP: J3001.45, R318.1
Grid_0_VFD: Q312.3, R324.1, VFD406.9
Grid_1_DSP: J3001.43, R310.1
Grid_1_VFD: Q308.3, R316.1, VFD404.9
Grid_2_DSP: J3001.41, R302.1
Grid_2_VFD: Q304.3, R308.1, VFD402.9
Grid_3_DSP: J3001.39, R317.1
Grid_3_VFD: Q311.3, R323.1, VFD405.9
Grid_4_DSP: J3001.37, R309.1
Grid_4_VFD: Q307.3, R315.1, VFD403.9
Grid_5_DSP: J3001.35, R301.1
Grid_5_VFD: Q303.3, R307.1, VFD401.9
I2C_DSP_SCL: J3001.59, U501.19, U1001.2, U1302.10
I2C_DSP_SDA: J3001.57, U501.20, U1001.1, U1302.7
unnamed: C603.1, U603.4
unnamed: C603.2, R601.2, U603.3
unnamed: C604.1, U604.4
unnamed: C604.2, R602.2, U604.3
unnamed: C605.1, U601.5, U603.5, U603.6
unnamed: C606.1, U602.5, U604.5, U604.6
unnamed: C607.1, R605.1, U605.1
unnamed: C608.1, R606.1, U606.1
unnamed: C803.1, U803.4
unnamed: C803.2, R801.2, U803.3
unnamed: C804.1, U804.4
unnamed: C804.2, R802.2, U804.3
unnamed: C805.1, U801.5, U803.5, U803.6
unnamed: C806.1, U802.5, U804.5, U804.6
unnamed: C807.1, R805.1, U805.1
unnamed: C808.1, R806.1, U806.1
unnamed: C902.1, U902.4
unnamed: C902.2, R901.2, U902.3
unnamed: C903.1, U901.5, U902.5, U902.6
unnamed: C904.1, R903.1, U903.1
unnamed: C1301.1, C1302.1, C1303.1, C1304.1, D1301.1, R1301.1, R1302.1, U1301.8
unnamed: D501.2, R501.2
unnamed: D502.2, R502.2
unnamed: D503.2, R503.2
unnamed: D504.2, R504.2
unnamed: D505.2, R505.2
unnamed: D506.2, R506.2
unnamed: D507.2, R507.2
unnamed: D508.2, R508.2
unnamed: D509.2, R509.2
unnamed: D510.2, R510.2
unnamed: D511.2, R511.2
unnamed: Q201.1, R201.2
unnamed: Q201.3, R204.2
unnamed: Q202.1, R202.2
unnamed: Q202.3, R206.2
unnamed: Q203.1, R203.2, R204.1
unnamed: Q204.1, R205.2, R206.1
unnamed: Q205.1, R209.2
unnamed: Q205.3, R212.2
unnamed: Q206.1, R210.2
unnamed: Q206.3, R214.2
unnamed: Q207.1, R211.2, R212.1
unnamed: Q208.1, R213.2, R214.1
unnamed: Q209.1, R217.2
unnamed: Q209.3, R220.2
unnamed: Q210.1, R218.2
unnamed: Q210.3, R222.2
unnamed: Q211.1, R219.2, R220.1
unnamed: Q212.1, R221.2, R222.1
unnamed: Q213.1, R225.2
unnamed: Q213.3, R228.2
unnamed: Q214.1, R226.2
unnamed: Q214.3, R230.2
unnamed: Q215.1, R227.2, R228.1
unnamed: Q216.1, R229.2, R230.1
unnamed: Q301.1, R301.2
unnamed: Q301.3, R304.2
unnamed: Q302.1, R302.2
unnamed: Q302.3, R306.2
unnamed: Q303.1, R303.2, R304.1
unnamed: Q304.1, R305.2, R306.1
unnamed: Q305.1, R309.2
unnamed: Q305.3, R312.2
unnamed: Q306.1, R310.2
unnamed: Q306.3, R314.2
unnamed: Q307.1, R311.2, R312.1
unnamed: Q308.1, R313.2, R314.1
unnamed: Q309.1, R317.2
unnamed: Q309.3, R320.2
unnamed: Q310.1, R318.2
unnamed: Q310.3, R322.2
unnamed: Q311.1, R319.2, R320.1
unnamed: Q312.1, R321.2, R322.1
unnamed: Q1101.1, R1101.2
unnamed: Q1101.3, R1103.2
unnamed: Q1102.1, R1102.2, R1103.1
unnamed: Q1102.3, R1104.1, R1105.2
unnamed: Q1103.1, R1108.2
unnamed: Q1103.3, R1110.2
unnamed: Q1104.1, R1109.2, R1110.1
unnamed: Q1104.3, R1111.1, R1112.2
unnamed: Q1105.1, R1115.2
unnamed: Q1105.3, R1117.2
unnamed: Q1106.1, R1116.2, R1117.1
unnamed: Q1106.3, R1118.1, R1119.2
unnamed: Q1107.1, R1120.2
unnamed: Q1107.3, R1122.2
unnamed: Q1108.1, R1121.2, R1122.1
unnamed: Q1108.3, R1123.1, R1124.2
unnamed: R601.1, SW601.1
unnamed: R602.1, SW602.1
unnamed: R603.1, R605.2, U603.1
unnamed: R604.1, R606.2, U604.1
unnamed: R801.1, SW801.1
unnamed: R802.1, SW802.1
unnamed: R803.1, R805.2, U803.1
unnamed: R804.1, R806.2, U804.1
unnamed: R901.1, SW901.1
unnamed: R902.1, R903.2, U902.1
unnamed: R1106.2, R1107.1, VFD1101.7
unnamed: R1113.2, R1114.1, VFD1102.7
unnamed: R1301.2, U1301.5, U1302.9
unnamed: R1302.2, U1301.6, U1302.8
unnamed: R1303.1, R1304.2, U1302.3
Set_Alarm_LED: R508.1, U501.4
Set_Brightness_LED: R511.1, U501.1
Set_Date_LED: R504.1, U501.8
Set_Time_LED: R502.1, U501.11
Set_Weekday_LED: R506.1, U501.6

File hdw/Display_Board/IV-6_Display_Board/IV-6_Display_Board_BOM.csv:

Item,Qty,Reference(s),Value,LibPart,Footprint,Datasheet,Dielectric,Digi-Key PN,Tolerance,Voltage,Wattage,display_footprint
1,19,"C501, C601, C602, C605, C606, C609, C610, C801, C802, C805, C806, C809, C810, C901, C903, C905, C1001, C1304, C1305",0.1uF,Custom_Library:C_Custom,Capacitors_SMD:C_0603,,X7R,311-1344-1-ND,,50V,,603
2,5,"C603, C604, C803, C804, C902",10nF,Custom_Library:C_Custom,Capacitors_SMD:C_0603,,X7R,1276-1921-1-ND,,50V,,603
3,10,"C607, C608, C807, C808, C904, C1201, C1202, C1301, C1302, C1303",10uF,Custom_Library:C_Custom,Capacitors_SMD:C_0603,,X5R,490-14372-1-ND,,10V,,603
4,1,C1203,1uF,Custom_Library:C_Custom,Capacitors_SMD:C_1210,,X7R,399-17668-1-ND,,100V,,1210
5,11,"D501, D502, D503, D504, D505, D506, D507, D508, D509, D510, D511",Cyan,Device:LED,LEDs:LED_0603,~,,754-2180-1-ND,,,,
6,1,D1301,MBR0530,Diode:MBR0530,Diode_SMD:D_SOD-123,http://www.mccsemi.com/up_pdf/MBR0520~MBR0580(SOD123).pdf,,MBR0530T1GOSCT-ND,,,,
7,1,DOC501,0x20,Custom_Library:I2C_Address,,,,,,,,
8,1,DOC1001,0x1F,Custom_Library:I2C_Address,,,,,,,,
9,1,DOC1301,0x3F,Custom_Library:I2C_Address,,,,,,,,
10,8,"H1401, H1402, H1403, H1404, H1405, H1406, H1407, H1408",MountingHole,Mechanical:MountingHole,MountingHole:MountingHole_3mm,~,,,,,,
11,1,J3001,DSP_IO_Connector,Connector_Generic:Conn_02x30_Odd_Even,Custom Footprints Library:ERM8-030-09.0-L-DV-TR,~,,ERM8-030-09.0-L-DV-K-TR,,,,
12,18,"Q201, Q202, Q205, Q206, Q209, Q210, Q213, Q214, Q301, Q302, Q305, Q306, Q309, Q310, Q1101, Q1103, Q1105, Q1107",PMSTA06,Transistor_BJT:BC847W,TO_SOT_Packages_SMD:SOT-323_SC-70,,,1727-6293-1-ND,,,,
13,18,"Q203, Q204, Q207, Q208, Q211, Q212, Q215, Q216, Q303, Q304, Q307, Q308, Q311, Q312, Q1102, Q1104, Q1106, Q1108",BC856W,Transistor_BJT:BC856W,TO_SOT_Packages_SMD:SOT-323_SC-70,,,1727-4865-1-ND,,,,
14,18,"R201, R202, R209, R210, R217, R218, R225, R226, R301, R302, R309, R310, R317, R318, R1101, R1108, R1115, R1120",10k,Device:R,Resistors_SMD:R_0603,,,P10.0KHCT-ND,1%,,1/10W,603
15,18,"R203, R205, R211, R213, R219, R221, R227, R229, R303, R305, R311, R313, R319, R321, R1102, R1109, R1116, R1121",220k,Device:R,Resistors_SMD:R_0603,,,P220KHCT-ND,1%,,1/10W,603
16,18,"R204, R206, R212, R214, R220, R222, R228, R230, R304, R306, R312, R314, R320, R322, R1103, R1110, R1117, R1122",68k,Device:R,Resistors_SMD:R_0603,,,P68KDBCT-ND,1%,,1/10W,603
17,18,"R207, R208, R215, R216, R223, R224, R231, R232, R307, R308, R315, R316, R323, R324, R1104, R1111, R1118, R1123",100k,Device:R,Resistors_SMD:R_0603,,,P16019CT-ND,1%,,1/10W,603
18,16,"R501, R502, R503, R504, R505, R506, R507, R508, R509, R510, R511, R601, R602, R801, R802, R901",499,Custom_Library:R_Custom,Resistors_SMD:R_0603,,,P499HCT-ND,1%,,1/10W,603
19,20,"R603, R604, R605, R606, R803, R804, R805, R806, R902, R903, R1105, R1106, R1107, R1112, R1113, R1114, R1119, R1124, R1301, R1302",10k,Custom_Library:R_Custom,Resistors_SMD:R_0603,,,RMCF0603FT10K0CT-ND,1%,,1/10W,603
20,1,R1303,392k,Custom_Library:R_Custom,Resistors_SMD:R_0603,,,311-392KHRCT-ND,1%,,1/10W,603
21,1,R1304,1M,Custom_Library:R_Custom,Resistors_SMD:R_0603,,,311-1.00MHRCT-ND,1%,,1/10W,603
22,5,"SW601, SW602, SW801, SW802, SW901",Cap_Touch,Custom_Library:Cap_Touch,Custom Footprints Library:Capacitive_Touch_Pad,,,,,,,
23,1,U501,TCA9555RGER,Interface_Expansion:TCA9555RGER,Package_DFN_QFN:QFN-24-1EP_4x4mm_P0.5mm_EP2.6x2.6mm,http://www.ti.com/lit/ds/symlink/tca9555.pdf,,296-44537-1-ND,,,,
24,5,"U601, U602, U801, U802, U901",TLV71333PDBV,IV-6_Display_Board-rescue:TLV71333PDBV-Regulator_Linear,Package_TO_SOT_SMD:SOT-23-5,http://www.ti.com/lit/ds/symlink/tlv713p.pdf,,296-35591-1-ND,,,,
25,5,"U603, U604, U803, U804, U902",AT42QT1010-TSHR,Sensor_Touch:AT42QT1010-TSHR,TO_SOT_Packages_SMD:SOT-23-6,http://ww1.microchip.com/downloads/en/DeviceDoc/Atmel-9541-A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,,AT42QT1010-TSHRCT-ND,,,,
26,5,"U605, U606, U805, U806, U903",74LVC1G97,Custom_Library:74LVC1G97_Power_BUF,Package_TO_SOT_SMD:SOT-363_SC-70-6,http://www.ti.com/lit/ds/symlink/sn74lvc1g97.pdf,,296-17671-1-ND,,,,
27,1,U1001,MCP9804,Custom_Library:MCP9804,Package_DFN_QFN:DFN-8-1EP_3x2mm_P0.5mm_EP1.75x1.45mm,http://ww1.microchip.com/downloads/en/DeviceDoc/22203b.pdf,,MCP9804T-E/MCCT-ND,,,,
28,1,U1301,DS1683,Custom_Library:DS1683,Housings_SOIC:SOIC-8_3.9x4.9mm_Pitch1.27mm,https://datasheets.maximintegrated.com/en/ds/DS1683.pdf,,DS1683S+-ND,,,,
29,1,U1302,LTC4316DD,Custom_Library:LTC4316DD,Housings_DFN_QFN:DFN-10-1EP_3x3mm_Pitch0.5mm,https://www.analog.com/media/en/technical-documentation/data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,,LTC4316IDD#PBF-ND,,,,
30,6,"VFD401, VFD402, VFD403, VFD404, VFD405, VFD406",IV-6,vfd:IV-6,Custom Footprints Library:IV-6,,,,,,,
31,2,"VFD1101, VFD1102",IV-1,Custom_Library:IV-1,Custom Footprints Library:IV-1,,,,,,,

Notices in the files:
parts and their libraries:
Copyright 2016 Accelerated Designs. All rights reserved.
